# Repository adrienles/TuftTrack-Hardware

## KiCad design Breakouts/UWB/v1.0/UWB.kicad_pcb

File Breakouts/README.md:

# Breakout Boards
---
This directory contains the various breakout boards designed to facilitate the development of TuftTrackers and TuftAnchors. They are all licensed under the CERN-OHL-W-2.0 license.

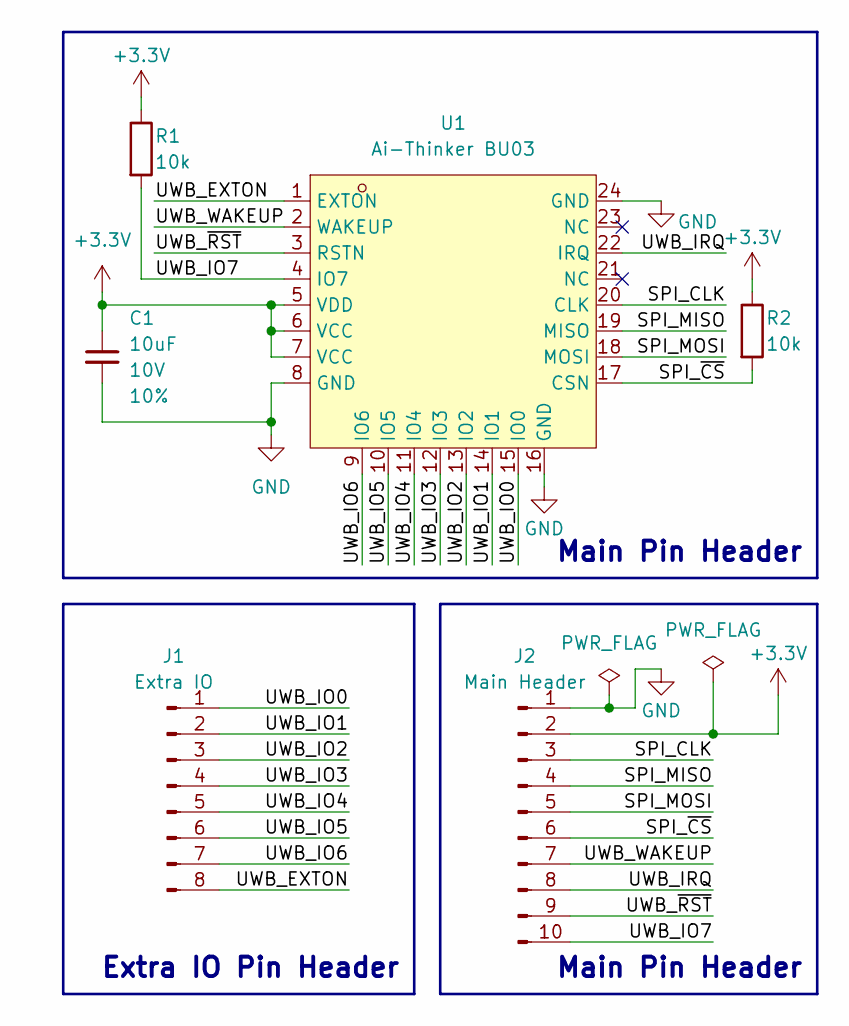
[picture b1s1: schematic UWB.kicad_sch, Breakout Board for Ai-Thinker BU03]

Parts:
C1: 10uF; C_0603_1608Metric_Pad1.08x0.95mm_HandSolder; Voltage 10V; Tolerance 10%
J1: Extra IO; PinHeader_1x08_P2.54mm_Vertical
J2: Main Header; PinHeader_1x10_P2.54mm_Vertical
R1, R2: 10k; R_0603_1608Metric_Pad0.98x0.95mm_HandSolder
U1: Ai-Thinker BU03; WIRELM-SMD_BU03; LCSC Part C42419011

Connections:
+3.3V: C1.1, J2.2, R1.1, R2.1, U1.5 (VDD), U1.6 (VCC), U1.7 (VCC)
/SPI_CLK: J2.3, U1.20 (CLK)
/SPI_MISO: J2.4, U1.19 (MISO)
/SPI_MOSI: J2.5, U1.18 (MOSI)
/SPI_~CS: J2.6, R2.2, U1.17 (CSN)
/UWB_EXTON: J1.8, U1.1 (EXTON)
/UWB_IO0: J1.1, U1.15 (IO0)
/UWB_IO1: J1.2, U1.14 (IO1)
/UWB_IO2: J1.3, U1.13 (IO2)
/UWB_IO3: J1.4, U1.12 (IO3)
/UWB_IO4: J1.5, U1.11 (IO4)
/UWB_IO5: J1.6, U1.10 (IO5)
/UWB_IO6: J1.7, U1.9 (IO6)
/UWB_IO7: J2.10, R1.2, U1.4 (IO7)
/UWB_IRQ: J2.8, U1.22 (IRQ)
/UWB_WAKEUP: J2.7, U1.2 (WAKEUP)
/UWB_~RST: J2.9, U1.3 (RSTN)
GND: C1.2, J2.1, U1.8 (GND), U1.16 (GND), U1.24 (GND)

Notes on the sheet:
Main Pin Header
Extra IO Pin Header

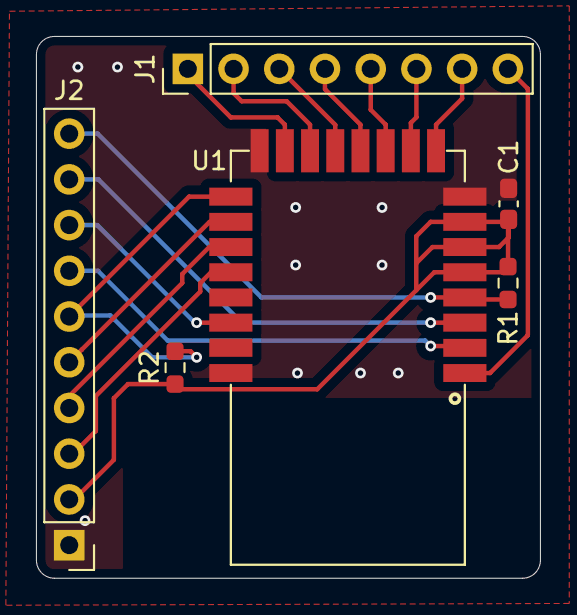
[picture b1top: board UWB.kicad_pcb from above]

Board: 2 copper layers, 28.0 x 30.1 mm, 6 parts (0 on the bottom side), 18 nets.

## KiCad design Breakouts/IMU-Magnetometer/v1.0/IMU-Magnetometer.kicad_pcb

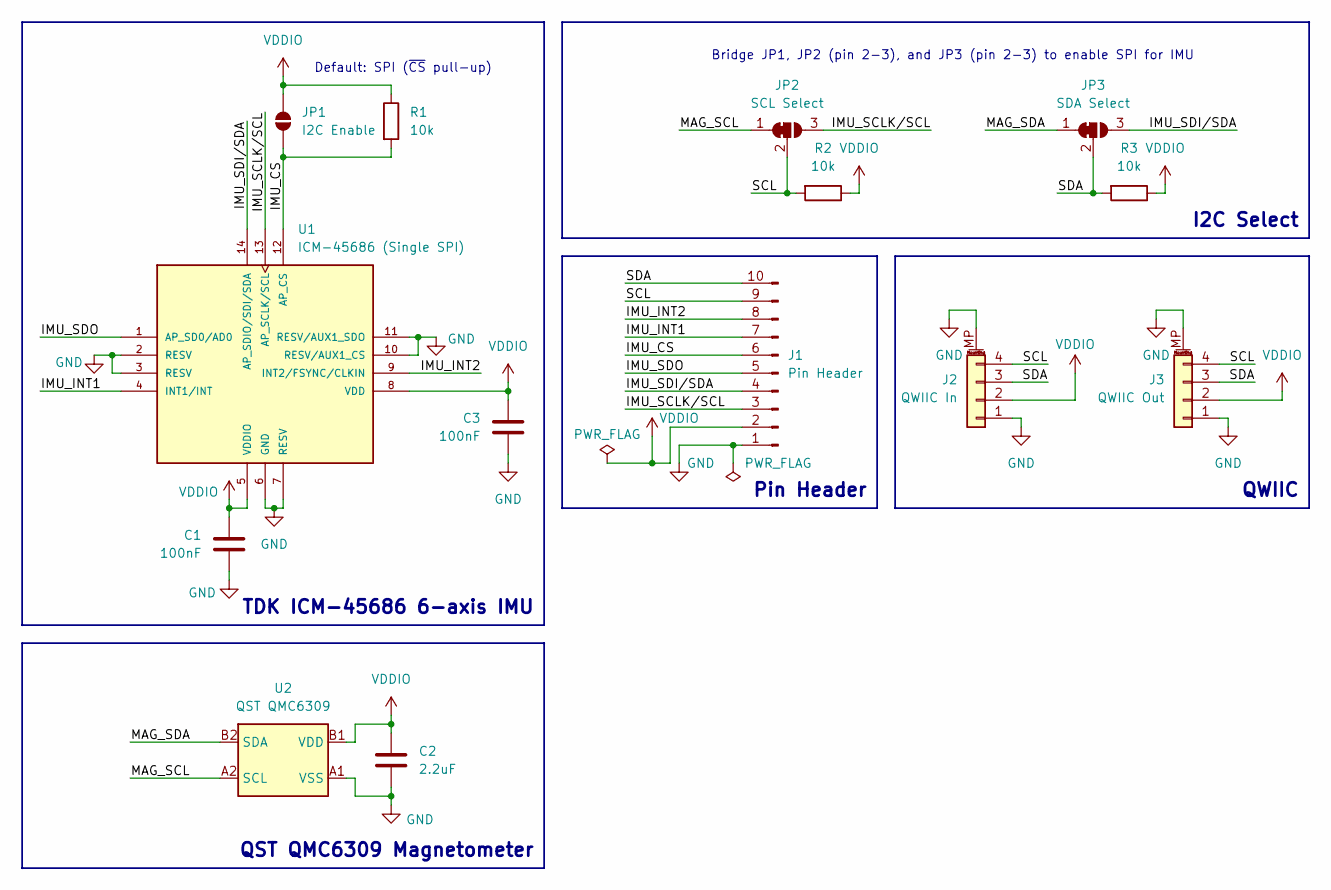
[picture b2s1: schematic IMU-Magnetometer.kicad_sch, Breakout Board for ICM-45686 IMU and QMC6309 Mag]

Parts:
C1, C3: 100nF; C_0603_1608Metric_Pad1.08x0.95mm_HandSolder
C2: 2.2uF; C_0603_1608Metric_Pad1.08x0.95mm_HandSolder
J1: Pin Header; PinHeader_1x10_P2.54mm_Vertical
J2: QWIIC In; JST_SH_SM04B-SRSS-TB_1x04-1MP_P1.00mm_Horizontal
J3: QWIIC Out; JST_SH_SM04B-SRSS-TB_1x04-1MP_P1.00mm_Horizontal
JP1: I2C Enable; SolderJumper-2_P1.3mm_Open_RoundedPad1.0x1.5mm
JP2: SCL Select; SolderJumper-3_P1.3mm_Bridged12_RoundedPad1.0x1.5mm_NumberL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
JP3: SDA Select; SolderJumper-3_P1.3mm_Bridged12_RoundedPad1.0x1.5mm_NumberL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
R1, R2, R3: 10k; R_0603_1608Metric_Pad0.98x0.95mm_HandSolder
U1: ICM-45686 (Single SPI); IC_ICM-45686; PARTREV 0.2
U2: QST QMC6309; X1-WLB0808-4_L0.8-W0.8-P0.40-TL

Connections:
/IMU_CS: J1.6, JP1.1 (A), R1.2, U1.12 (AP_CS)
/IMU_INT1: J1.7, U1.4 (INT1/INT)
/IMU_INT2: J1.8, U1.9 (INT2/FSYNC/CLKIN)
/IMU_SCLK/SCL: J1.3, JP2.3 (B), U1.13 (AP_SCLK/SCL)
/IMU_SDI/SDA: J1.4, JP3.3 (B), U1.14 (AP_SDIO/SDI/SDA)
/IMU_SDO: J1.5, U1.1 (AP_SD0/AD0)
/MAG_SCL: JP2.1 (A), U2.A2 (SCL)
/MAG_SDA: JP3.1 (A), U2.B2 (SDA)
/SCL: J1.9, J2.4, J3.4, JP2.2 (C), R2.2
/SDA: J1.10, J2.3, J3.3, JP3.2 (C), R3.2
GND: C1.2, C2.2, C3.2, J1.1, J2.1, J2.MP (MountPin), J3.1, J3.MP (MountPin), U1.2 (RESV), U1.3 (RESV), U1.6 (GND), U1.7 (RESV), U1.10 (RESV/AUX1_CS), U1.11 (RESV/AUX1_SDO), U2.A1 (VSS)
VDDIO: C1.1, C2.1, C3.1, J1.2, J2.2, J3.2, JP1.2 (B), R1.1, R2.1, R3.1, U1.5 (VDDIO), U1.8 (VDD), U2.B1 (VDD)

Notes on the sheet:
QWIIC
Pin Header
Bridge JP1, JP2 (pin 2-3), and JP3 (pin 2-3) to enable SPI for IMU
Default: SPI (~{CS} pull-up)
QST QMC6309 Magnetometer
I2C Select
TDK ICM-45686 6-axis IMU

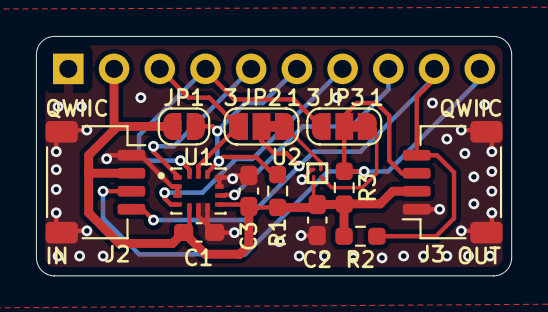
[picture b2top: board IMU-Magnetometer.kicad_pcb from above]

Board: 2 copper layers, 26.4 x 13.3 mm, 14 parts (1 on the bottom side), 12 nets.

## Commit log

2025-09-06 ADD : KiCad Projects, various schematic blocks, and IMU + Mag schematics
2025-09-10 ADD : Completed layout and routing of V1 IMU + Mag test breakout
2025-09-10 ADD : Initial KiCAD project for PMU Breakout with configured paths
2025-09-19 ADD : Completed BU03 Breakout. MOD : Project structure.

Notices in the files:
Breakouts/IMU-Magnetometer/V1/IMU-Magnetometer.kicad_sch:
© CC BY-SA 4.0
Breakouts/UWB/v1.0/UWB.kicad_pcb:
© Adrien Lesage
CC BY-SA 4.0
